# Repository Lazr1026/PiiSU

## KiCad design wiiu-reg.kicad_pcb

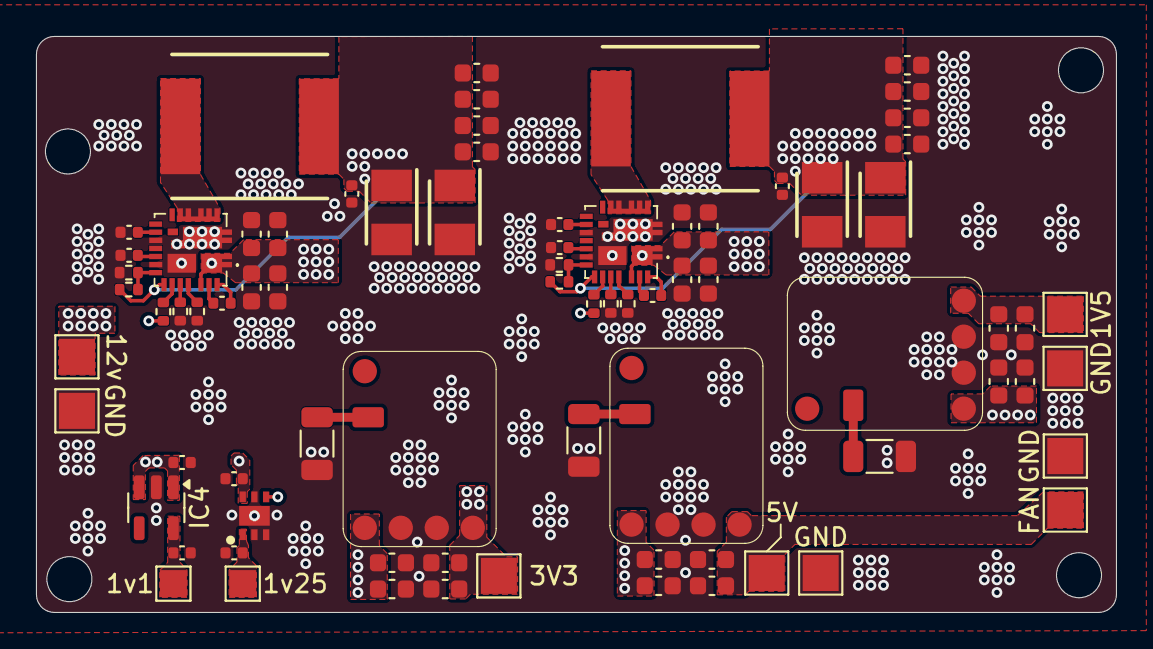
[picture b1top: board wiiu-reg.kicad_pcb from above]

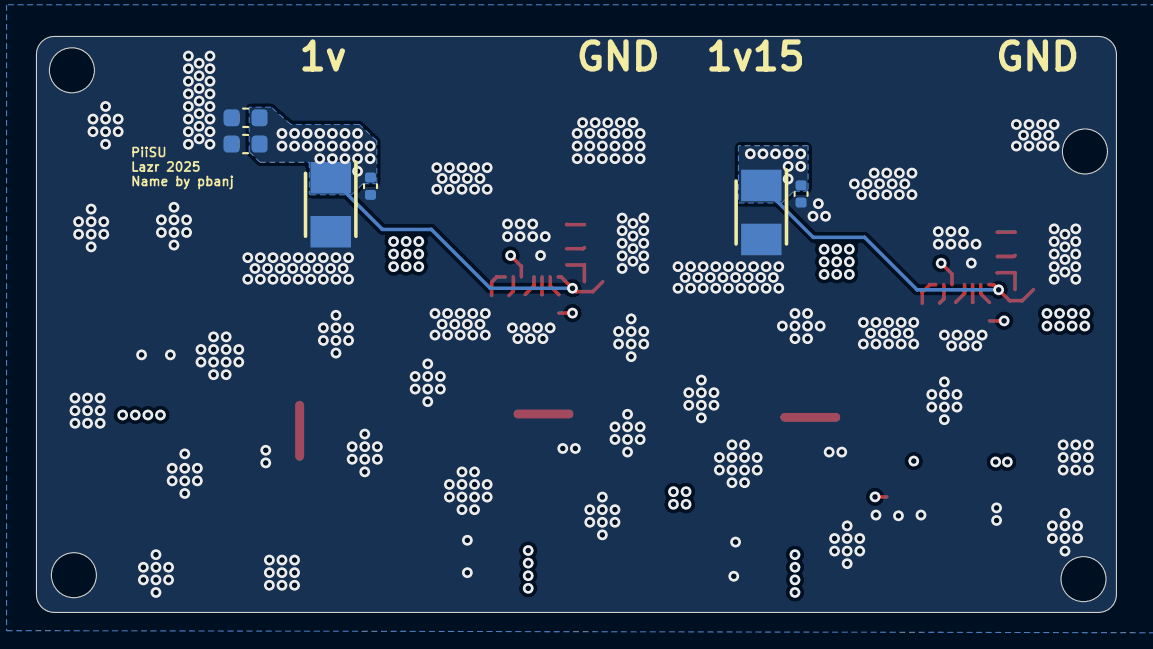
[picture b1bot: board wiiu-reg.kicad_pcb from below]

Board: 4 copper layers, 60.0 x 32.0 mm, 83 parts (6 on the bottom side), 30 nets.

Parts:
1V5: 1v5; TestPoint_Pad_2.0x2.0mm
1v1: 1v1; TestPoint_Pad_1.5x1.5mm
1v25: 1v25; TestPoint_Pad_1.5x1.5mm
3V3: 3v3; TestPoint_Pad_2.0x2.0mm
5V: 5v; TestPoint_Pad_2.0x2.0mm
12v: VIN; TestPoint_Pad_2.0x2.0mm
C1, C2, C3, C19, C20, C21: F930J107KBA
C4, C5, C16, C22, C23, C32: 0.1uF; C_0402_1005Metric
C6, C7, C8, C9, C10, C11, C12, C13, C14, C15, C24, C25, C26, C27, C28, C29, C30, C31, C35, C36, C37, C38, C39, C40, C41, C42, C43, C44, C45, C46: 22uF; C_0603_1608Metric
C17, C33, C47, C48, C49, C50: 1uF; C_0402_1005Metric
C18, C34: 2.2uF; C_0402_1005Metric
FAN: 5v; TestPoint_Pad_2.0x2.0mm
GND: GND; TestPoint_Pad_2.0x2.0mm
GND#2, GND#3, GND#4: GND; TestPoint_Pad_2.0x2.0mm
IC1, IC2: SIC431AED-T1-GE3; SIC431AEDT1GE3
IC3: TPS7A26125DRVR
IC4: TCR2EF11,LM(CT; SOT-23-5
L1, L2: MPXV1D0840L1R0
R1: 6.67k; R_0402_1005Metric
R2, R7: 100k; R_0402_1005Metric
R3: 10k; R_0402_1005Metric
R4, R5, R9, R10: 510k; R_0402_1005Metric
R6: 11k; R_0402_1005Metric
R8: 12k; R_0402_1005Metric
R11: 7.5k; R_1206_3216Metric
R12: 2.61k; R_1206_3216Metric
R13: 1.58k; R_1206_3216Metric
U1, U2, U3: Reggie

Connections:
+1V0: C1.1 (+), C2.1 (+), C3.1 (+), C4.1, C5.1, C6.1, C7.1, C8.1, C9.1, C10.1, C11.1, IC1.18 (VOUT), L1.2, R1.1
+1V1: 1v1.1, C50.1, IC4.5 (VOUT)
+1V5: 1V5.1, C37.1, C38.1, U1.2 (VOUT)
+1V15: C19.1 (+), C20.1 (+), C21.1 (+), C22.1, C23.1, C24.1, C25.1, C26.1, C27.1, IC2.18 (VOUT), L2.2, R6.1
+1V25: 1v25.1, C47.1, IC3.1 (OUT)
+3V3: 3V3.1, C41.1, C42.1, C48.1, C49.1, IC3.4 (EN), IC3.6 (IN), IC4.1 (VIN), IC4.3 (Control), U2.2 (VOUT)
+5V: 5V.1, C45.1, C46.1, FAN.1, U3.2 (VOUT)
GND: C1.2 (-), C2.2 (-), C3.2 (-), C4.2, C5.2, C6.2, C7.2, C8.2, C9.2, C10.2, C11.2, C12.2, C13.2, C14.2, C15.2, C17.2, C18.2, C19.2 (-), C20.2 (-), C21.2 (-), C22.2, C23.2, C24.2, C25.2, C26.2, C27.2, C28.2, C29.2, C30.2, C31.2, C33.2, C34.2, C35.2, C36.2, C37.2, C38.2, C39.2, C40.2, C41.2, C42.2, C43.2, C44.2, C45.2, C46.2, C47.2, C48.2, C49.2, C50.2, GND.1, GND#2.1, GND#3.1, GND#4.1, IC1.3 (PGND_1), IC1.4 (PGND_2), IC1.13 (PGND_3), IC1.16 (AGND_1), IC1.25 (AGND_2), IC1.27 (PGND_4), IC1.28 (PGND_5), IC2.3 (PGND_1), IC2.4 (PGND_2), IC2.13 (PGND_3), IC2.16 (AGND_1), IC2.25 (AGND_2), IC2.27 (PGND_4), IC2.28 (PGND_5), IC3.2 (FB), IC3.3 (PG), IC3.5 (GND), IC3.7 (EP), IC4.2 (GND), R3.2, R4.2, R5.2, R8.2, R9.2, R10.2, R11.2, R12.2, R13.2, U1.3 (GND), U2.3 (GND), U3.3 (GND)
unnamed: C16.1, IC1.23 (BOOT)
unnamed: IC1.19 (EN), R2.2
unnamed: IC1.17 (FB), R1.2, R3.1
unnamed: IC1.21 (MODE1), R4.1
unnamed: IC1.20 (MODE2), R5.1
unnamed: C16.2, IC1.24 (PHASE)
unnamed: IC1.5 (SW_1), IC1.6 (SW_2), IC1.7 (SW_3), IC1.8 (SW_4), IC1.9 (SW_5), IC1.30 (SW_6), IC1.31 (SW_7), IC1.32 (SW_8), IC1.33 (SW_9), L1.1
unnamed: C17.1, IC1.15 (VDD)
unnamed: C18.1, IC1.12 (VDRV)
unnamed: C32.1, IC2.23 (BOOT)
unnamed: IC2.19 (EN), R7.2
unnamed: IC2.17 (FB), R6.2, R8.1
unnamed: IC2.21 (MODE1), R9.1
unnamed: IC2.20 (MODE2), R10.1
unnamed: C32.2, IC2.24 (PHASE)
unnamed: IC2.5 (SW_1), IC2.6 (SW_2), IC2.7 (SW_3), IC2.8 (SW_4), IC2.9 (SW_5), IC2.30 (SW_6), IC2.31 (SW_7), IC2.32 (SW_8), IC2.33 (SW_9), L2.1
unnamed: C33.1, IC2.15 (VDD)
unnamed: C34.1, IC2.12 (VDRV)
unnamed: R11.1, U1.4 (FB)
unnamed: R12.1, U2.4 (FB)
unnamed: R13.1, U3.4 (FB)
VIN: 12v.1, C12.1, C13.1, C14.1, C15.1, C28.1, C29.1, C30.1, C31.1, C35.1, C36.1, C39.1, C40.1, C43.1, C44.1, IC1.1 (VIN_1), IC1.2 (VIN_2), IC1.22 (VIN_3), IC1.26 (VIN_4), IC2.1 (VIN_1), IC2.2 (VIN_2), IC2.22 (VIN_3), IC2.26 (VIN_4), R2.1, R7.1, U1.1 (VIN), U2.1 (VIN), U3.1 (VIN)

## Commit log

2025-04-13 make thing hopefully suck less
2025-04-14 (hopefully) final layout!
2025-04-14 Fix some unrouted nets
2025-04-17 Complete redesign
2025-05-05 Forgot to add label silkscreen on the bottom
